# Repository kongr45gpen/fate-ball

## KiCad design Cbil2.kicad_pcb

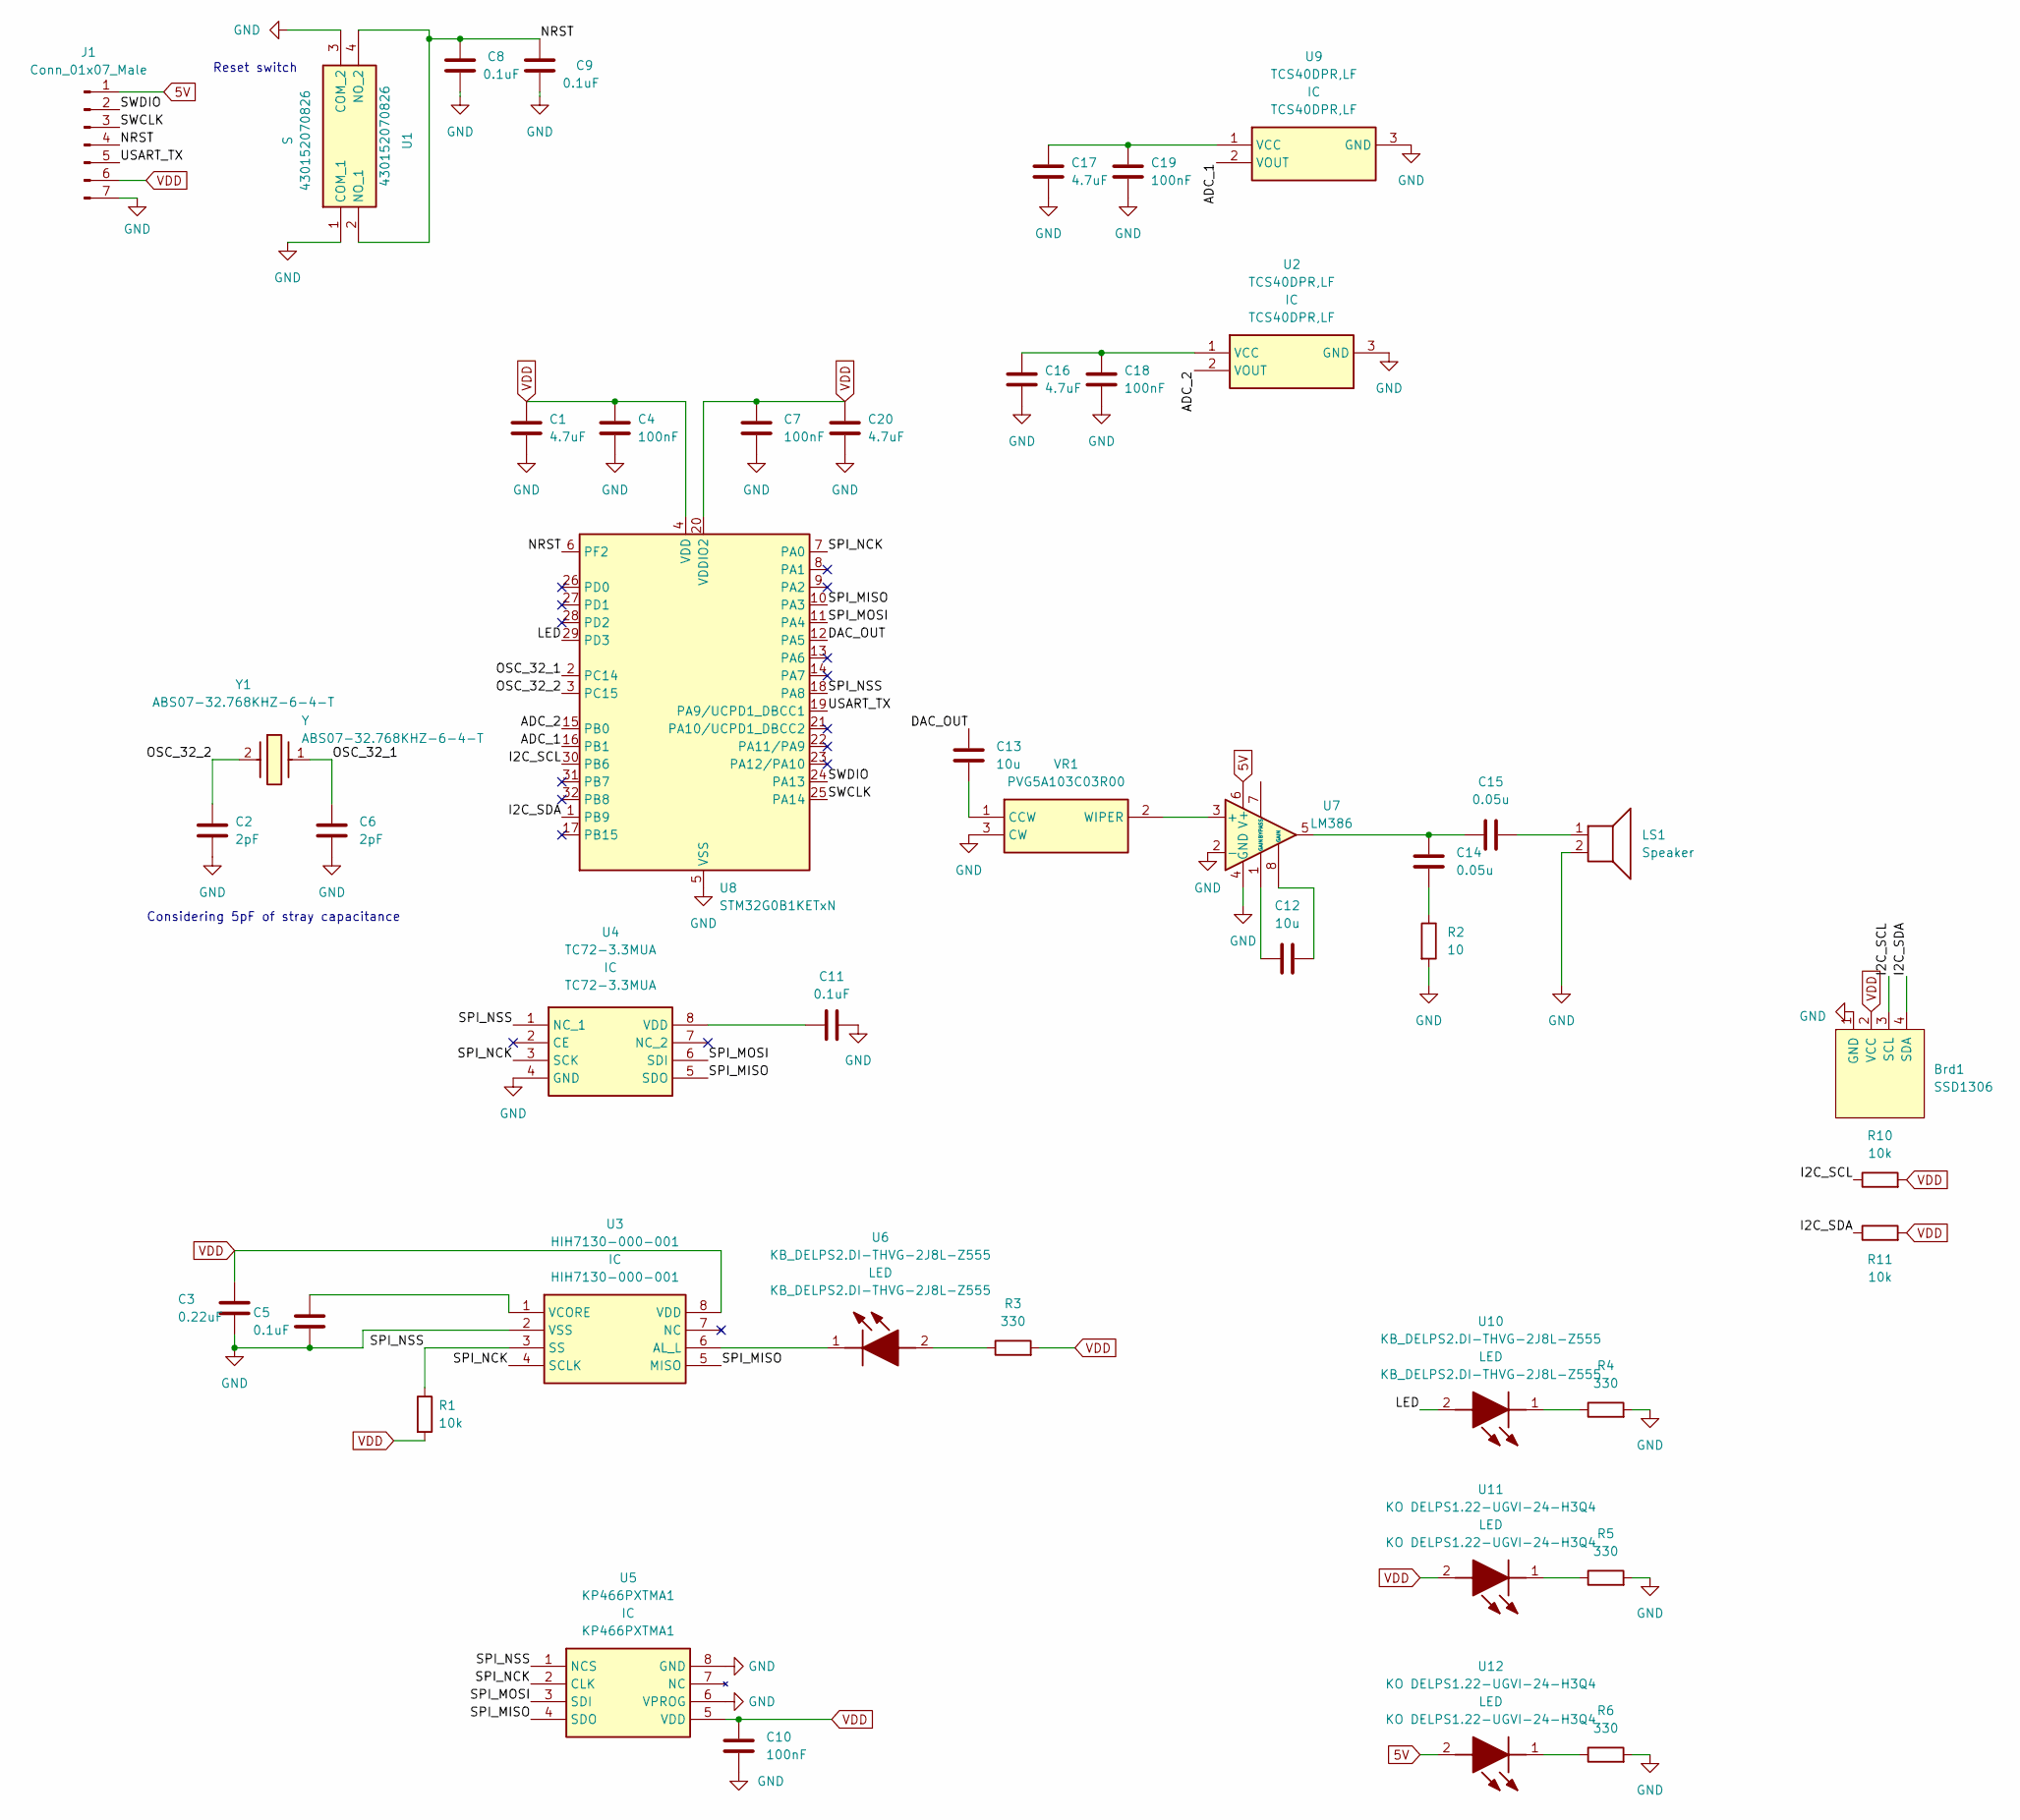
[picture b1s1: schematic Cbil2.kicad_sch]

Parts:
Brd1: SSD1306; 128x64OLED
C1, C16, C17, C20: 4.7uF; C_0603_1608Metric
C2, C6: 2pF; C_0603_1608Metric
C3: 0.22uF; C_0603_1608Metric
C4, C7, C10, C18, C19: 100nF; C_0603_1608Metric
C5, C8, C9, C11: 0.1uF; C_0603_1608Metric
C12, C13: 10u; C_0603_1608Metric
C14, C15: 0.05u; C_0603_1608Metric
J1: Conn_01x07_Male; PinHeader_1x07_P2.54mm_Vertical
LS1: Speaker; Speaker_CUI_CMR-1206S-67; MPN CMR-12062S-67
R1: 10k; C_0603_1608Metric
R2: 10; R_0603_1608Metric
R3, R4, R5, R6: 330; C_0603_1608Metric
R10, R11: 10k; R_0603_1608Metric_Pad0.98x0.95mm_HandSolder
U1: 430152070826; Mouser Part Number 710-430152070826
U2, U9: TCS40DPR,LF; SOTFL95P240X88-3N; Mouser Part Number 757-TCS40DPRLF
U3: HIH7130-000-001; Mouser Part Number 785-HIH7130-000-001
U4: TC72-3.3MUA; SOP65P490X110-8N; Mouser Part Number 579-TC72-3.3MUA
U5: KP466PXTMA1; Mouser Part Number 726-KP466PXTMA1
U6, U10: KB_DELPS2.DI-THVG-2J8L-Z555; KBDELPS2DITHVG2J8LZ555; Mouser Part Number 720-KBDELPS2DIA8693
U7: LM386; SOIC127P600X175-8N
U8: STM32G0B1KETxN; LQFP-32_7x7mm_P0.8mm
U11, U12: KO DELPS1.22-UGVI-24-H3Q4; KBDELPS2DITHVG2J8LZ555; Mouser Part Number 720-KODELPS122A3997
VR1: PVG5A103C03R00; PVG5A100C03R00; Mouser Part Number 81-PVG5A103C03R00
Y1: ABS07-32.768KHZ-6-4-T; ABS07; Mouser Part Number 815-ABS0732768KHZ64T

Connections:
5V: J1.1, U7.6 (V+), U12.2 (A)
/ADC_1: U8.16 (PB1), U9.2 (VOUT)
/ADC_2: U2.2 (VOUT), U8.15 (PB0)
/DAC_OUT: C13.1, U8.12 (PA5)
/I2C_SCL: Brd1.3 (SCL), U8.30 (PB6); also elsewhere on the board
/I2C_SDA: Brd1.4 (SDA), U8.1 (PB9); also elsewhere on the board
/LED: U8.29 (PD3), U10.2 (A)
/NRST: C8.1, C9.1, J1.4, U1.2 (NO_1), U1.4 (NO_2), U8.6 (PF2)
/OSC_32_1: C6.1, U8.2 (PC14), Y1.1 (X1)
/OSC_32_2: C2.1, U8.3 (PC15), Y1.2 (X2)
/SPI_MISO: U3.5 (MISO), U4.5 (SDO), U5.4 (SDO), U8.10 (PA3)
/SPI_MOSI: U4.6 (SDI), U5.3 (SDI), U8.11 (PA4)
/SPI_NCK: U3.4 (SCLK), U4.3 (SCK), U5.2 (CLK), U8.7 (PA0)
/SPI_NSS: R1.1, U3.3 (SS), U4.1 (NC_1), U5.1 (NCS), U8.18 (PA8)
/SWCLK: J1.3, U8.25 (PA14)
/SWDIO: J1.2, U8.24 (PA13)
/USART_TX: J1.5, U8.19 (PA9/UCPD1_DBCC1)
GND: Brd1.1 (GND), C1.2, C2.2, C3.2, C4.2, C5.2, C6.2, C7.2, C8.2, C9.2, C10.2, C11.2, C16.2, C17.2, C18.2, C19.2, C20.2, J1.7, LS1.2, R2.2, R4.2, R5.2, R6.2, U1.1 (COM_1), U1.3 (COM_2), U2.3 (GND), U3.2 (VSS), U4.4 (GND), U5.6 (VPROG), U5.8 (GND), U7.2 (-), U7.4 (GND), U8.5 (VSS), U9.3 (GND), VR1.3 (CW)
unnamed: C12.1, U7.8 (GAIN)
unnamed: C12.2, U7.1 (GAIN)
unnamed: C14.1, C15.1, U7.5
unnamed: C14.2, R2.1
unnamed: C15.2, LS1.1
unnamed: C16.1, C18.1, U2.1 (VCC)
unnamed: U3.6 (AL_L), U6.1 (K)
unnamed: C5.1, U3.1 (VCORE)
unnamed: C11.1, U4.8 (VDD)
unnamed: R3.1, U6.2 (A)
unnamed: U7.3 (+), VR1.2 (WIPER)
unnamed: C17.1, C19.1, U9.1 (VCC)
unnamed: R4.1, U10.1 (K)
unnamed: R5.1, U11.1 (K)
unnamed: R6.1, U12.1 (K)
unnamed: C13.2, VR1.1 (CCW)
VDD: Brd1.2 (VCC), C1.1, C3.1, C4.1, C7.1, C10.1, C20.1, J1.6, R1.2, R3.2, U3.8 (VDD), U5.5 (VDD), U8.4 (VDD), U8.20 (VDDIO2), U11.2 (A); also elsewhere on the board

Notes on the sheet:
Reset switch
Considering 5pF of stray capacitance

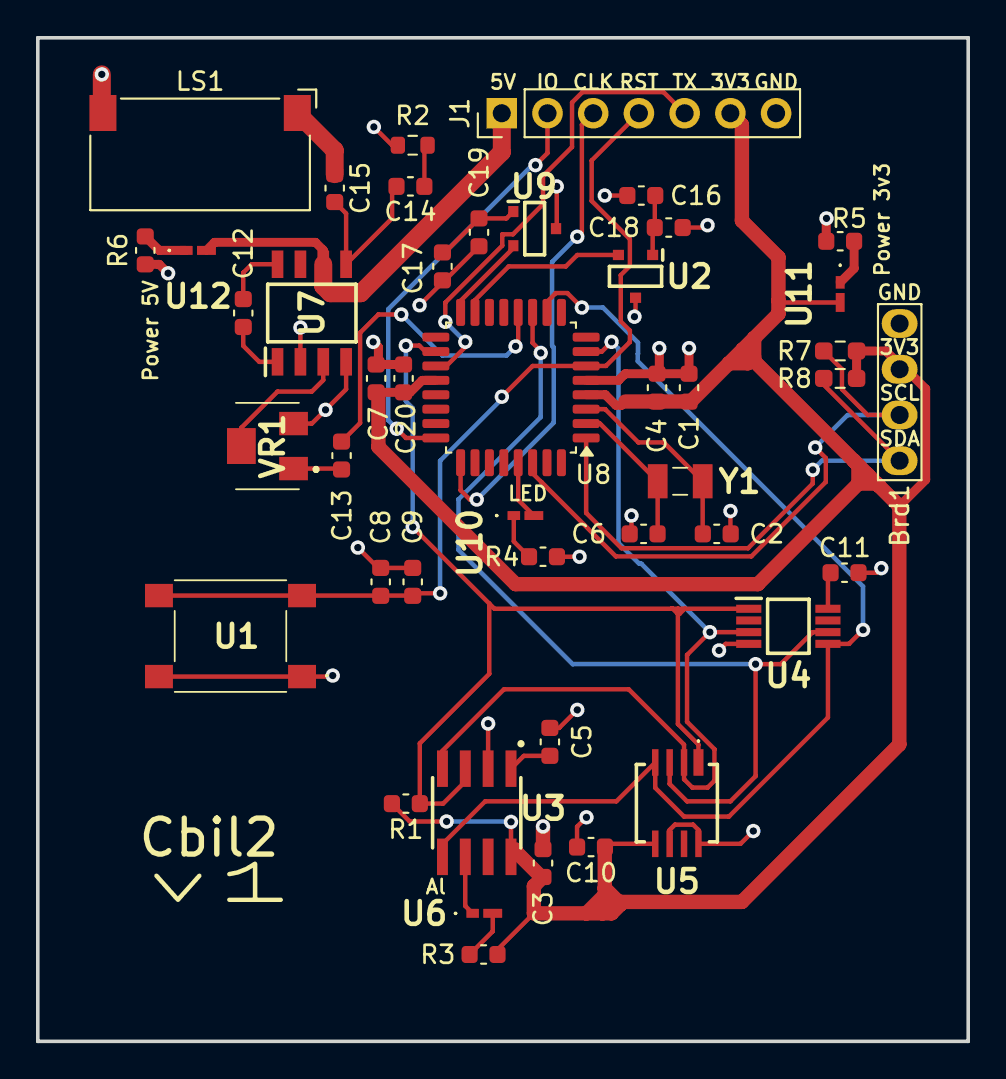
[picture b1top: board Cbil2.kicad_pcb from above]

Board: 2 copper layers, 51.7 x 55.8 mm, 45 parts (0 on the bottom side), 35 nets.

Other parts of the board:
R7, R8: 10k; R_0603_1608Metric_Pad0.98x0.95mm_HandSolder

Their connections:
/I2C_SCL: R7.1; also elsewhere on the board
/I2C_SDA: R8.1; also elsewhere on the board
VDD: R7.2, R8.2; also elsewhere on the board

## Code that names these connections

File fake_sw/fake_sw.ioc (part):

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Mcu.Name=STM32G0B1K(B-C-E)TxN
Mcu.Package=LQFP32
Mcu.UserName=STM32G0B1KETxN
PA5.Signal=COMP_DAC12_group
PB0.Mode=IN8
PB0.Signal=ADC1_IN8
PB1.Mode=IN9
PB1.Signal=ADC1_IN9
PB6.Mode=I2C
PB6.Signal=I2C1_SCL
PB9.Mode=I2C
PB9.Signal=I2C1_SDA
PD3.GPIOParameters=GPIO_Label
PD3.GPIO_Label=LED
PD3.Signal=GPIO_Output
RCC.HSE_VALUE=8000000
RCC.SYSCLKFreq_VALUE=16000000
board=custom

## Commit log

2024-03-01 Add audio amplifier
2024-03-03 PCB layout
2024-03-07 Add a few doodads
2024-03-07 Add a screen
2024-03-07 Update layout
2024-03-07 Add silkscreen
2024-04-04 Add software initial commit
2024-04-05 Start work on screen
2024-04-05 Advanced screen manipulation
2024-04-05 Add sounds
2024-04-05 Create LICENSE
